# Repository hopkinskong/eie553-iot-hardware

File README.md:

# eie553-iot-hardware
ESP32 IOT Smart Lock Device Hardware used in the course "EIE553 Security in Data Communication".

### Description ###
This repository contains full hardware source used in the IOT Smart Lock Device in EIE553 Course offered by The Hong Kong Polytechnic University.
For course related question please email me directly via university email.
You are welcomed to submit pull requests for improvements.

### Related Respositories ###
- [ESP32 Device Firmware](https://github.com/hopkinskong/eie553-iot-esp32-firmware)
- [(This Repository)Device Hardware Schematic and PCB](https://github.com/hopkinskong/eie553-iot-hardware)

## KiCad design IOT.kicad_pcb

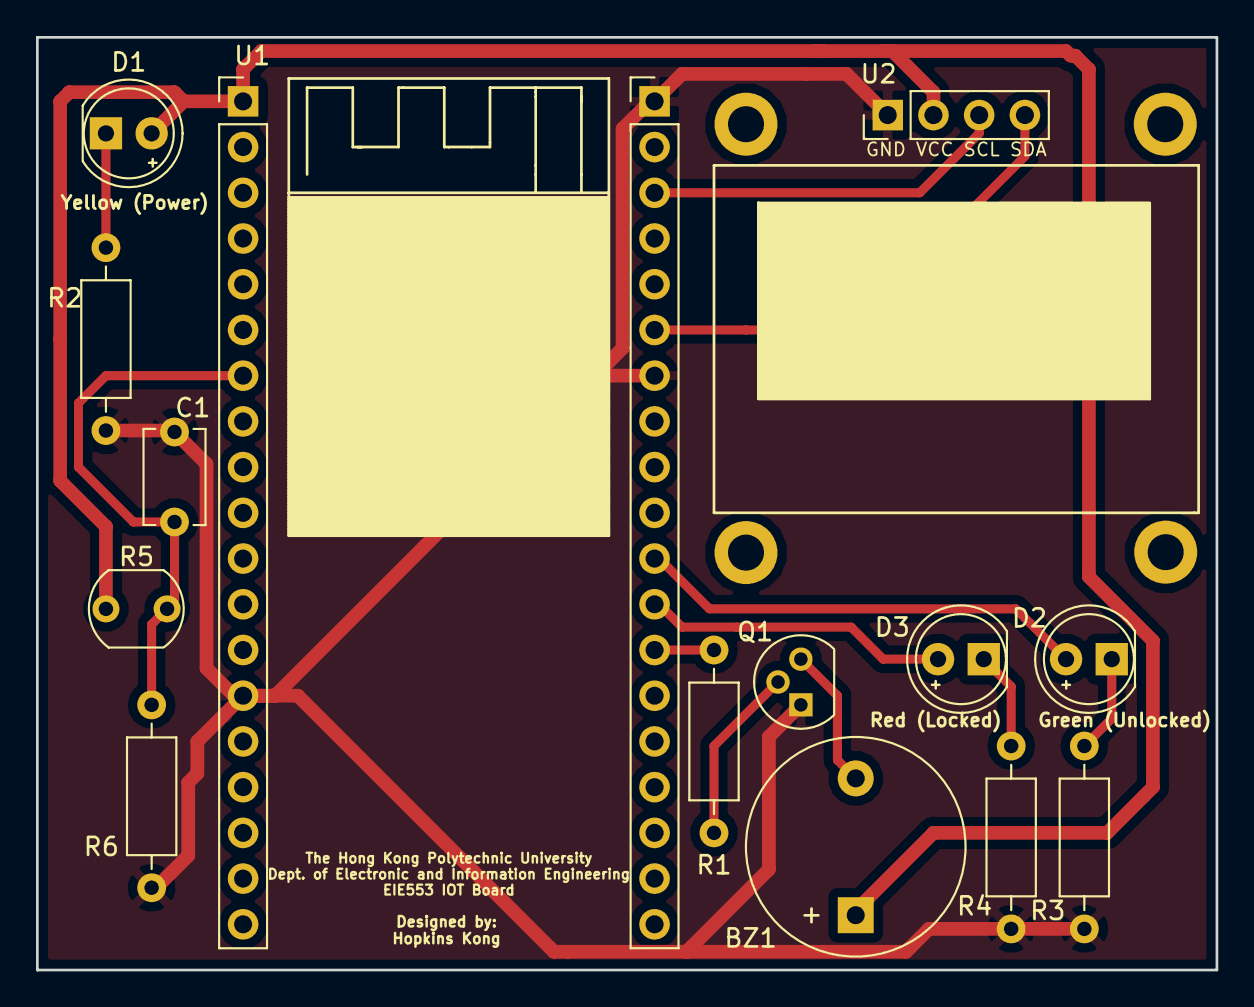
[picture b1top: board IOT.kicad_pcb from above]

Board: 2 copper layers, 65.5 x 51.8 mm, 14 parts (0 on the bottom side), 13 nets.

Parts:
BZ1: 3V3 Active Buzzer; Buzzer_12x9.5RM7.6
C1: 100n/50V; C_Disc_D5.1mm_W3.2mm_P5.00mm
D1: 5MM_YELLOW_LED; LED_D5.0mm
D2: 5MM_GREEN_LED; LED_D5.0mm
D3: 5MM_RED_LED; LED_D5.0mm
Q1: S8050; TO-92
R1: 1K/0.25W; R_Axial_DIN0207_L6.3mm_D2.5mm_P10.16mm_Horizontal
R2, R3, R4: 330R/0.25W; R_Axial_DIN0207_L6.3mm_D2.5mm_P10.16mm_Horizontal
R5: GL5506; R_LDR_5.1x4.3mm_P3.4mm_Vertical
R6: 10K/0.25W; R_Axial_DIN0207_L6.3mm_D2.5mm_P10.16mm_Horizontal
U1: NodeMCU-32S; nodemcu_esp32s
U2: 0.96Inch_OLED_4Pin; oled_4pin

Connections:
+3V3: BZ1.1, D1.2, R5.1, U1.1, U2.2
/BUZZER_CONTROL: R1.2, U1.26
/GREEN_LED: D2.2, U1.28
/LDR_ADC: C1.1, R5.2, R6.2, U1.7
/OLED_SCL: U1.36, U2.3
/OLED_SDA: U1.33, U2.4
/RED_LED: D3.2, U1.27
GND: C1.2, Q1.1, R2.1, R3.1, R4.1, R6.1, U1.14, U1.32, U1.38, U2.1
unnamed: BZ1.2, Q1.3
unnamed: D1.1, R2.2
unnamed: D2.1, R3.2
unnamed: D3.1, R4.2
unnamed: Q1.2, R1.1

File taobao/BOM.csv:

Source:,/media/root/Work Stuff/EIE553/IOT/IOT.sch,,,,
Date:,Sun Sep 23 15:01:01 2018,,,,
Tool:,Eeschema 5.0.0+dfsg1-1,,,,
Component Count:,14,,,,
Ref,Value,Footprint,Datasheet,Manufacturer,Vendor
BZ1,3V3 Active Buzzer (3.3V直插有源蜂鸣器),Buzzer_Beeper:Buzzer_12x9.5RM7.6,~,,
C1,100n/50V,Capacitor_THT:C_Disc_D5.1mm_W3.2mm_P5.00mm,~,,
D1,5MM_YELLOW_LED (5mm白发黄直插LED，透明圆头),LED_THT:LED_D5.0mm,~,,
D2,5MM_GREEN_LED (5mm白发绿直插LED，透明圆头),LED_THT:LED_D5.0mm,~,,
D3,5MM_RED_LED (5mm白发红直插LED，透明圆头),LED_THT:LED_D5.0mm,~,,
Q1,S8050 (S8050 三极管),Package_TO_SOT_THT:TO-92,~,,
R1,1K/0.25W,Resistor_THT:R_Axial_DIN0207_L6.3mm_D2.5mm_P10.16mm_Horizontal,~,,
R2,330R/0.25W,Resistor_THT:R_Axial_DIN0207_L6.3mm_D2.5mm_P10.16mm_Horizontal,~,,
R3,330R/0.25W,Resistor_THT:R_Axial_DIN0207_L6.3mm_D2.5mm_P10.16mm_Horizontal,~,,
R4,330R/0.25W,Resistor_THT:R_Axial_DIN0207_L6.3mm_D2.5mm_P10.16mm_Horizontal,~,,
R5,GL5506 (GL5506光敏电阻),OptoDevice:R_LDR_5.1x4.3mm_P3.4mm_Vertical,~,,
R6,10K/0.25W,Resistor_THT:R_Axial_DIN0207_L6.3mm_D2.5mm_P10.16mm_Horizontal,~,,
U1,Single_Row_2.54mm 19P_Female_Header*2 (单行2.54mm 19P 排母 * 2条),IOT:nodemcu_esp32s,,,
U2,Single_Row_2.54mm_4P_Female_Header*1 (单行2.54mm 4P 排母 * 1条 [另加M2铜柱，见原理图]),IOT:oled_4pin,,,
